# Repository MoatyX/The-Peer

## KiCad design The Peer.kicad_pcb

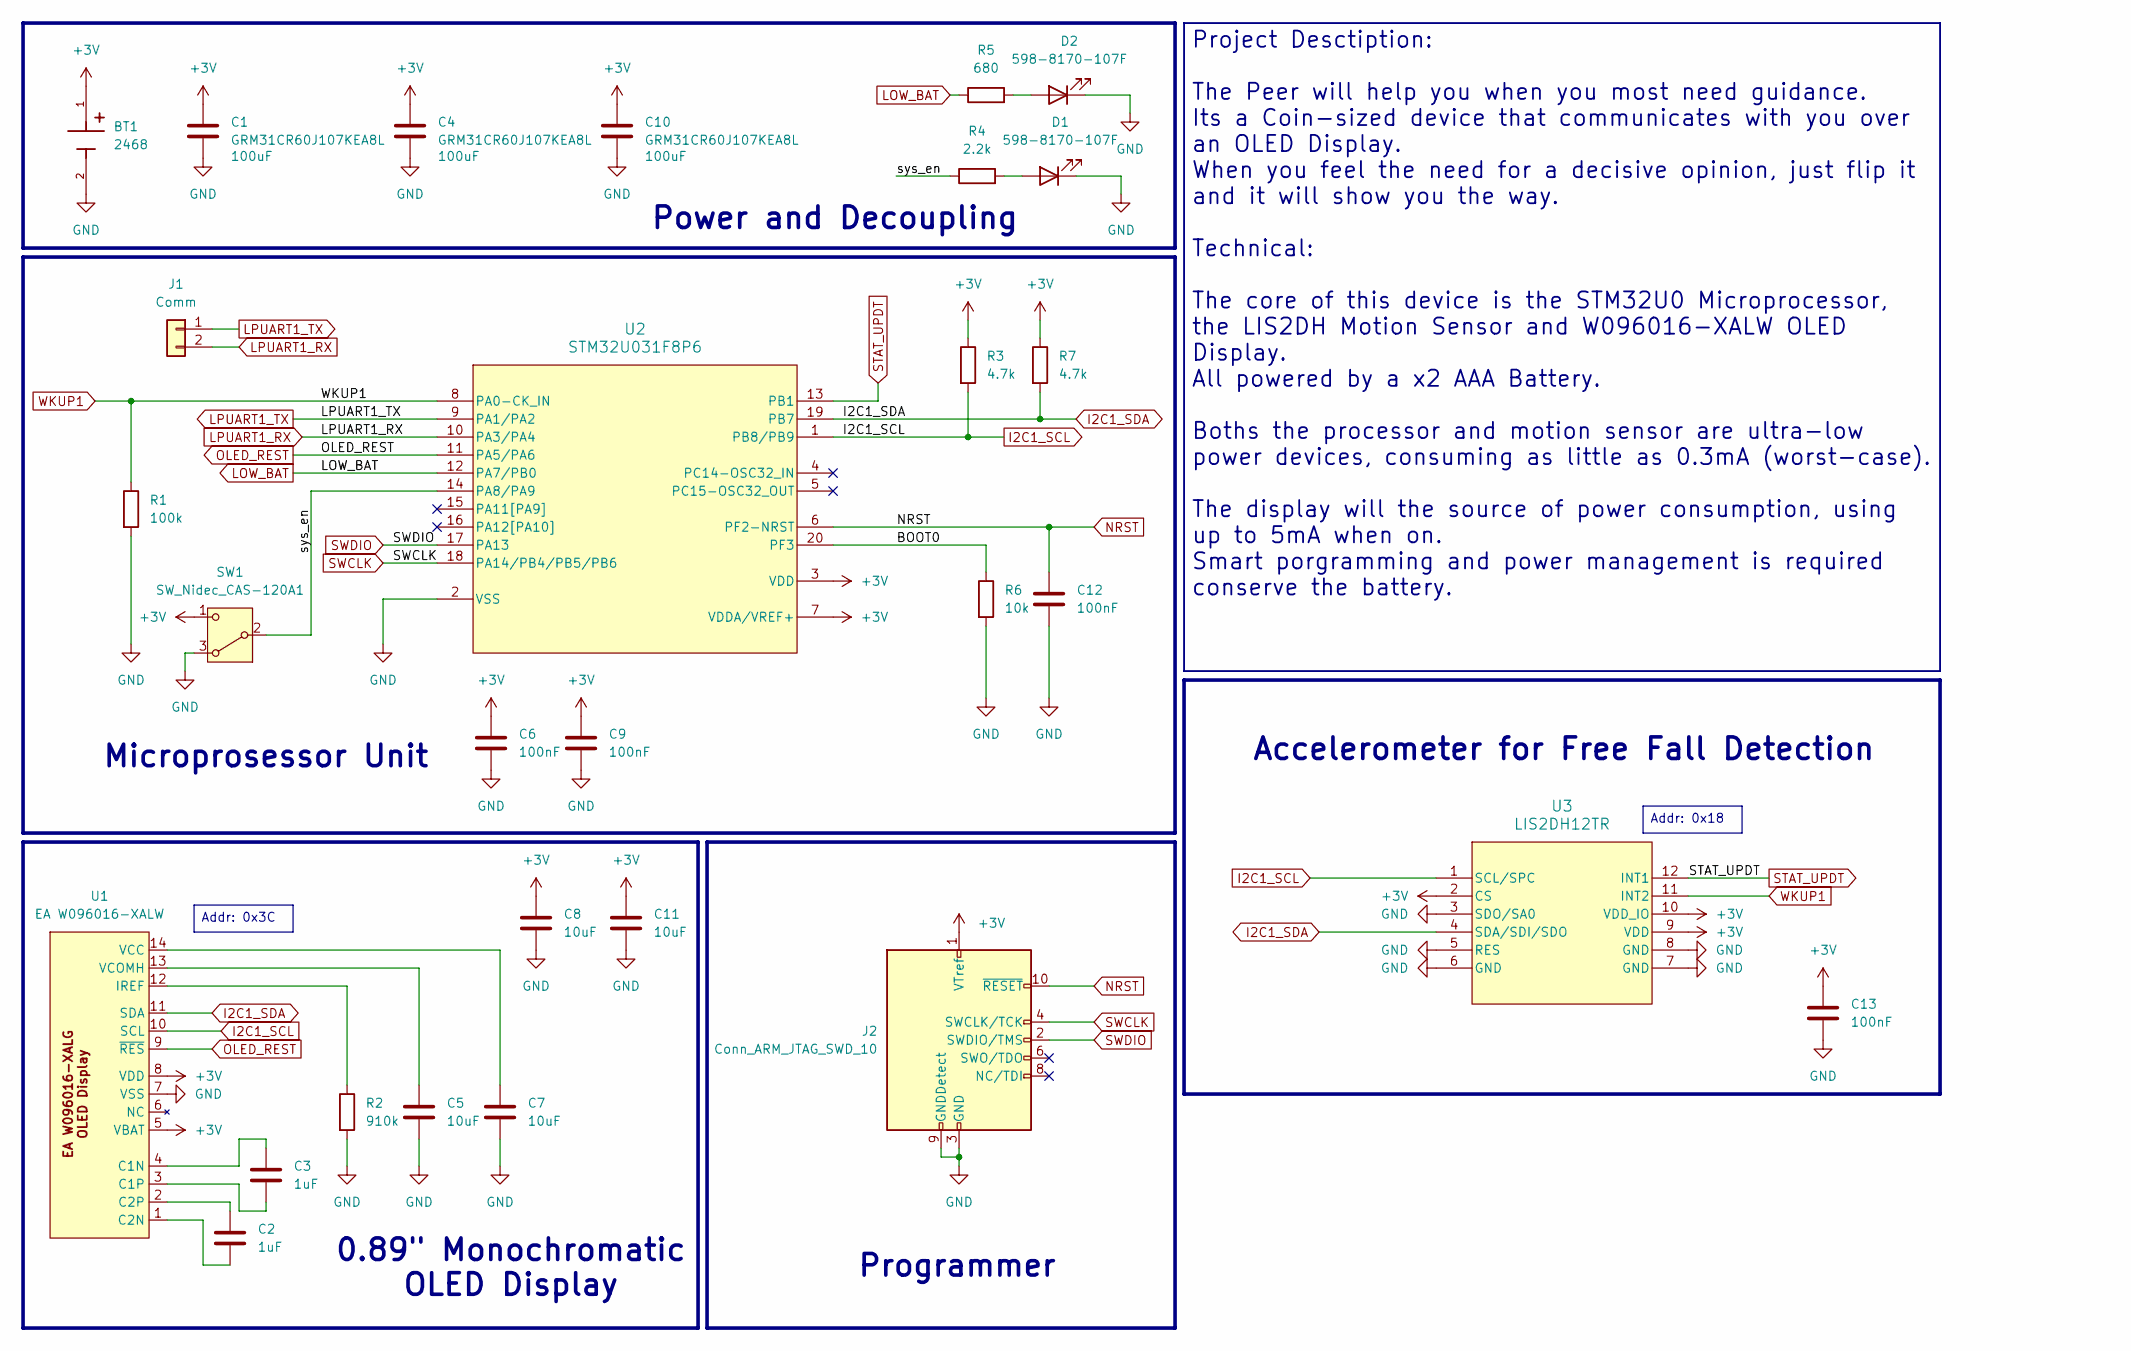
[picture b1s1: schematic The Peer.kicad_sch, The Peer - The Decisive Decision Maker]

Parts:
BT1: 2468; BatteryHolder_Keystone_2468_2xAAA; PARTREV H
C1, C4, C10: GRM31CR60J107KEA8L; C_1206_3216Metric_Pad1.33x1.80mm_HandSolder
C2, C3: 1uF; C_0402_1005Metric_Pad0.74x0.62mm_HandSolder
C5, C7, C8, C11: 10uF; C_0805_2012Metric_Pad1.18x1.45mm_HandSolder
C6, C9, C12, C13: 100nF; C_0402_1005Metric_Pad0.74x0.62mm_HandSolder
D1, D2: 598-8170-107F; LED_0805_2012Metric_Pad1.15x1.40mm_HandSolder
J1: Comm; PinHeader_1x02_P2.54mm_Vertical
J2: Conn_ARM_JTAG_SWD_10; SWD_2x5_Module_1.27mm
R1: 100k; R_0402_1005Metric_Pad0.72x0.64mm_HandSolder
R2: 910k; R_0402_1005Metric_Pad0.72x0.64mm_HandSolder
R3, R7: 4.7k; R_0402_1005Metric_Pad0.72x0.64mm_HandSolder
R4: 2.2k; R_0805_2012Metric_Pad1.20x1.40mm_HandSolder
R5: 680; R_0805_2012Metric_Pad1.20x1.40mm_HandSolder
R6: 10k; R_0402_1005Metric_Pad0.72x0.64mm_HandSolder
SW1: SW_Nidec_CAS-120A1; Nidec_Copal_CAS-120A
U1: EA W096016-XALW
U2: STM32U031F8P6; TSSOP-20_4.4x6.5mm_P0.65mm
U3: LIS2DH12TR; LGA-12_2x2mm_P0.5mm

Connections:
+3V: BT1.1, C1.1, C4.1, C6.1, C8.1, C9.1, C10.1, C11.1, C13.1, J2.1 (VTref), R3.1, R7.1, SW1.1 (C), U1.5 (VBAT), U1.8 (VDD), U2.3 (VDD), U2.7 (VDDA/VREF+), U3.2 (CS), U3.9 (VDD), U3.10 (VDD_IO)
/BOOT0: R6.1, U2.20 (PF3)
/sys_en: R4.1, SW1.2 (B), U2.14 (PA8/PA9)
GND: BT1.2, C1.2, C4.2, C5.1, C6.2, C7.1, C8.2, C9.2, C10.2, C11.2, C12.2, C13.2, D1.1 (K), D2.1 (K), J2.3 (GND), J2.5 (GND), J2.9 (GNDDetect), R1.2, R2.2, R6.2, SW1.3 (A), U1.7 (VSS), U2.2 (VSS), U3.3 (SDO/SA0), U3.5 (RES), U3.6 (GND), U3.7 (GND), U3.8 (GND)
I2C1_SCL: R3.2, U1.10 (SCL), U2.1 (PB8/PB9), U3.1 (SCL/SPC)
I2C1_SDA: R7.2, U1.11 (SDA), U2.19 (PB7), U3.4 (SDA/SDI/SDO)
LOW_BAT: R5.1, U2.12 (PA7/PB0)
LPUART1_RX: J1.2, U2.10 (PA3/PA4)
LPUART1_TX: J1.1, U2.9 (PA1/PA2)
NRST: C12.1, J2.10 (~RESET), U2.6 (PF2-NRST)
unnamed: D1.2 (A), R4.2
unnamed: D2.2 (A), R5.2
unnamed: C3.2, U1.4 (C1N)
unnamed: C3.1, U1.3 (C1P)
unnamed: C2.1, U1.1 (C2N)
unnamed: C2.2, U1.2 (C2P)
unnamed: R2.1, U1.12 (IREF)
unnamed: C7.2, U1.14 (VCC)
unnamed: C5.2, U1.13 (VCOMH)
OLED_REST: U1.9 (~RES), U2.11 (PA5/PA6)
STAT_UPDT: U2.13 (PB1), U3.12 (INT1)
SWCLK: J2.4 (SWCLK/TCK), U2.18 (PA14/PB4/PB5/PB6)
SWDIO: J2.2 (SWDIO/TMS), U2.17 (PA13)
WKUP1: R1.1, U2.8 (PA0-CK_IN), U3.11 (INT2)

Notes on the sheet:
0.89" Monochromatic OLED Display
Programmer
Accelerometer for Free Fall Detection
Power and Decoupling
Microprosessor Unit
Addr: 0x18
Project Desctiption: The Peer will help you when you most need guidance. Its a Coin-sized device that communicates with you over an OLED Display. When you feel the need for a decisive opinion, just flip it and it will show you the way. Technical: The core of this device is the STM32U0 Microprocesso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
Addr: 0x3C

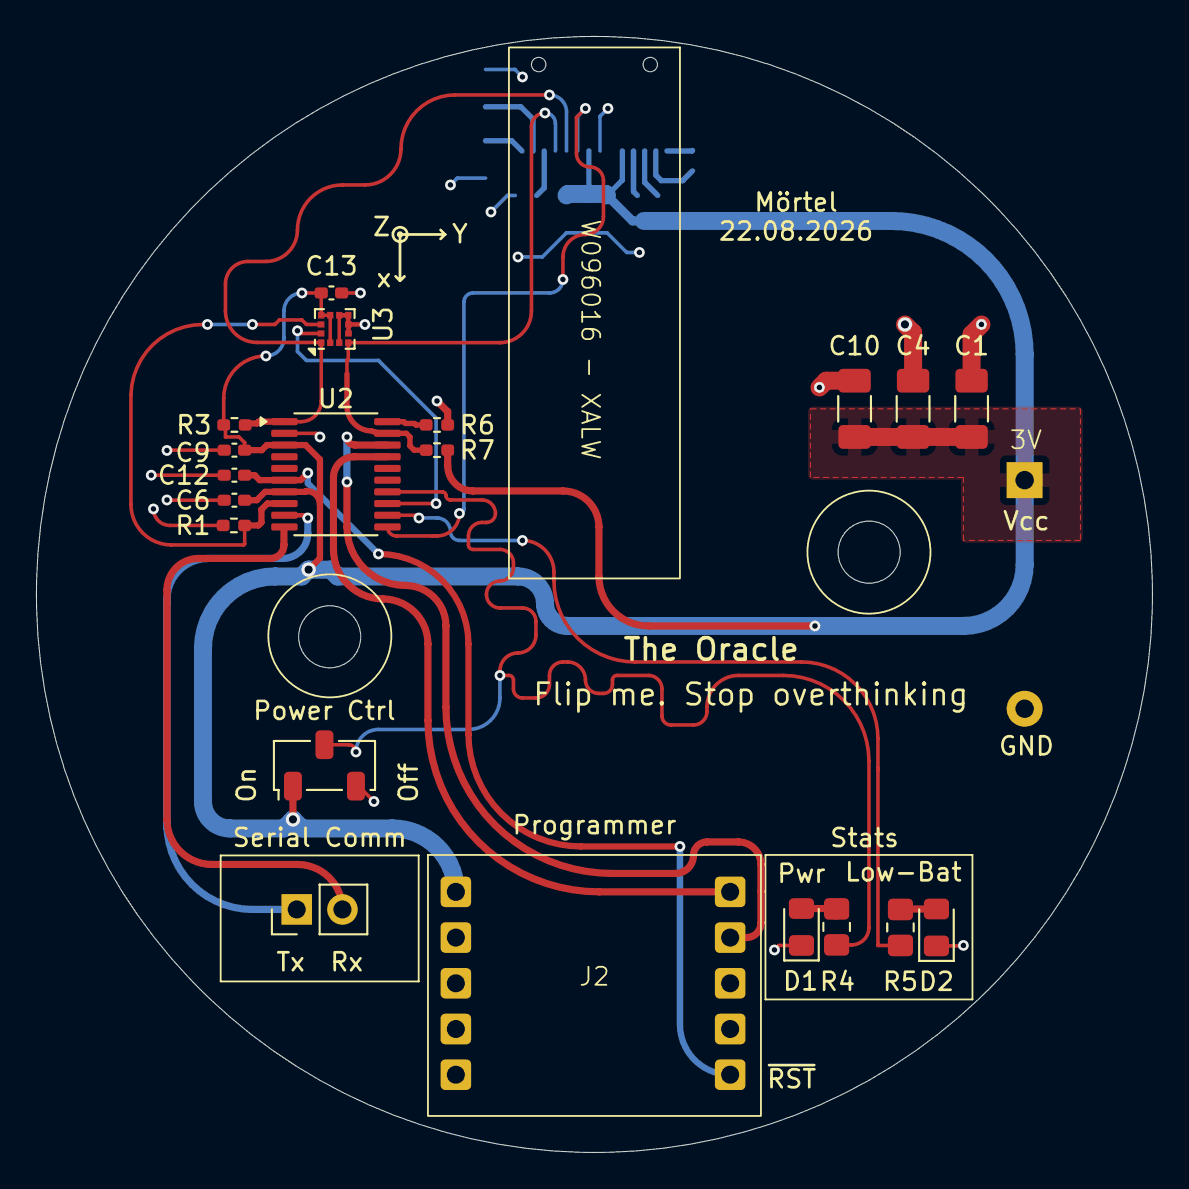
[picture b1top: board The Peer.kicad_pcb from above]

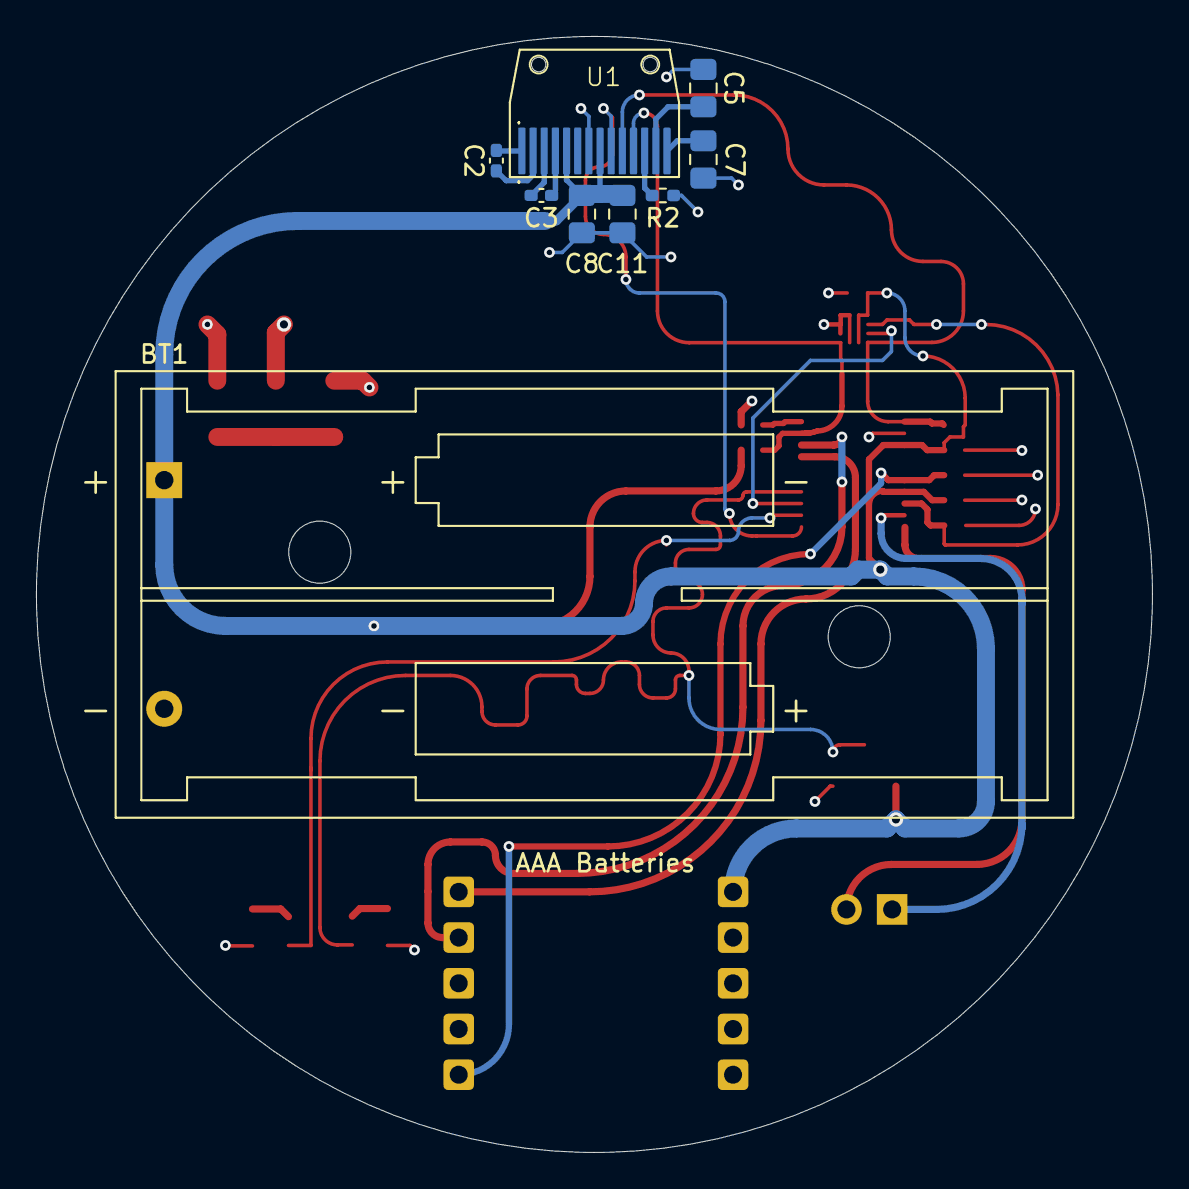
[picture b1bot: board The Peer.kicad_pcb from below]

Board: 4 copper layers, 62.0 x 62.0 mm, 29 parts (9 on the bottom side), 24 nets.
